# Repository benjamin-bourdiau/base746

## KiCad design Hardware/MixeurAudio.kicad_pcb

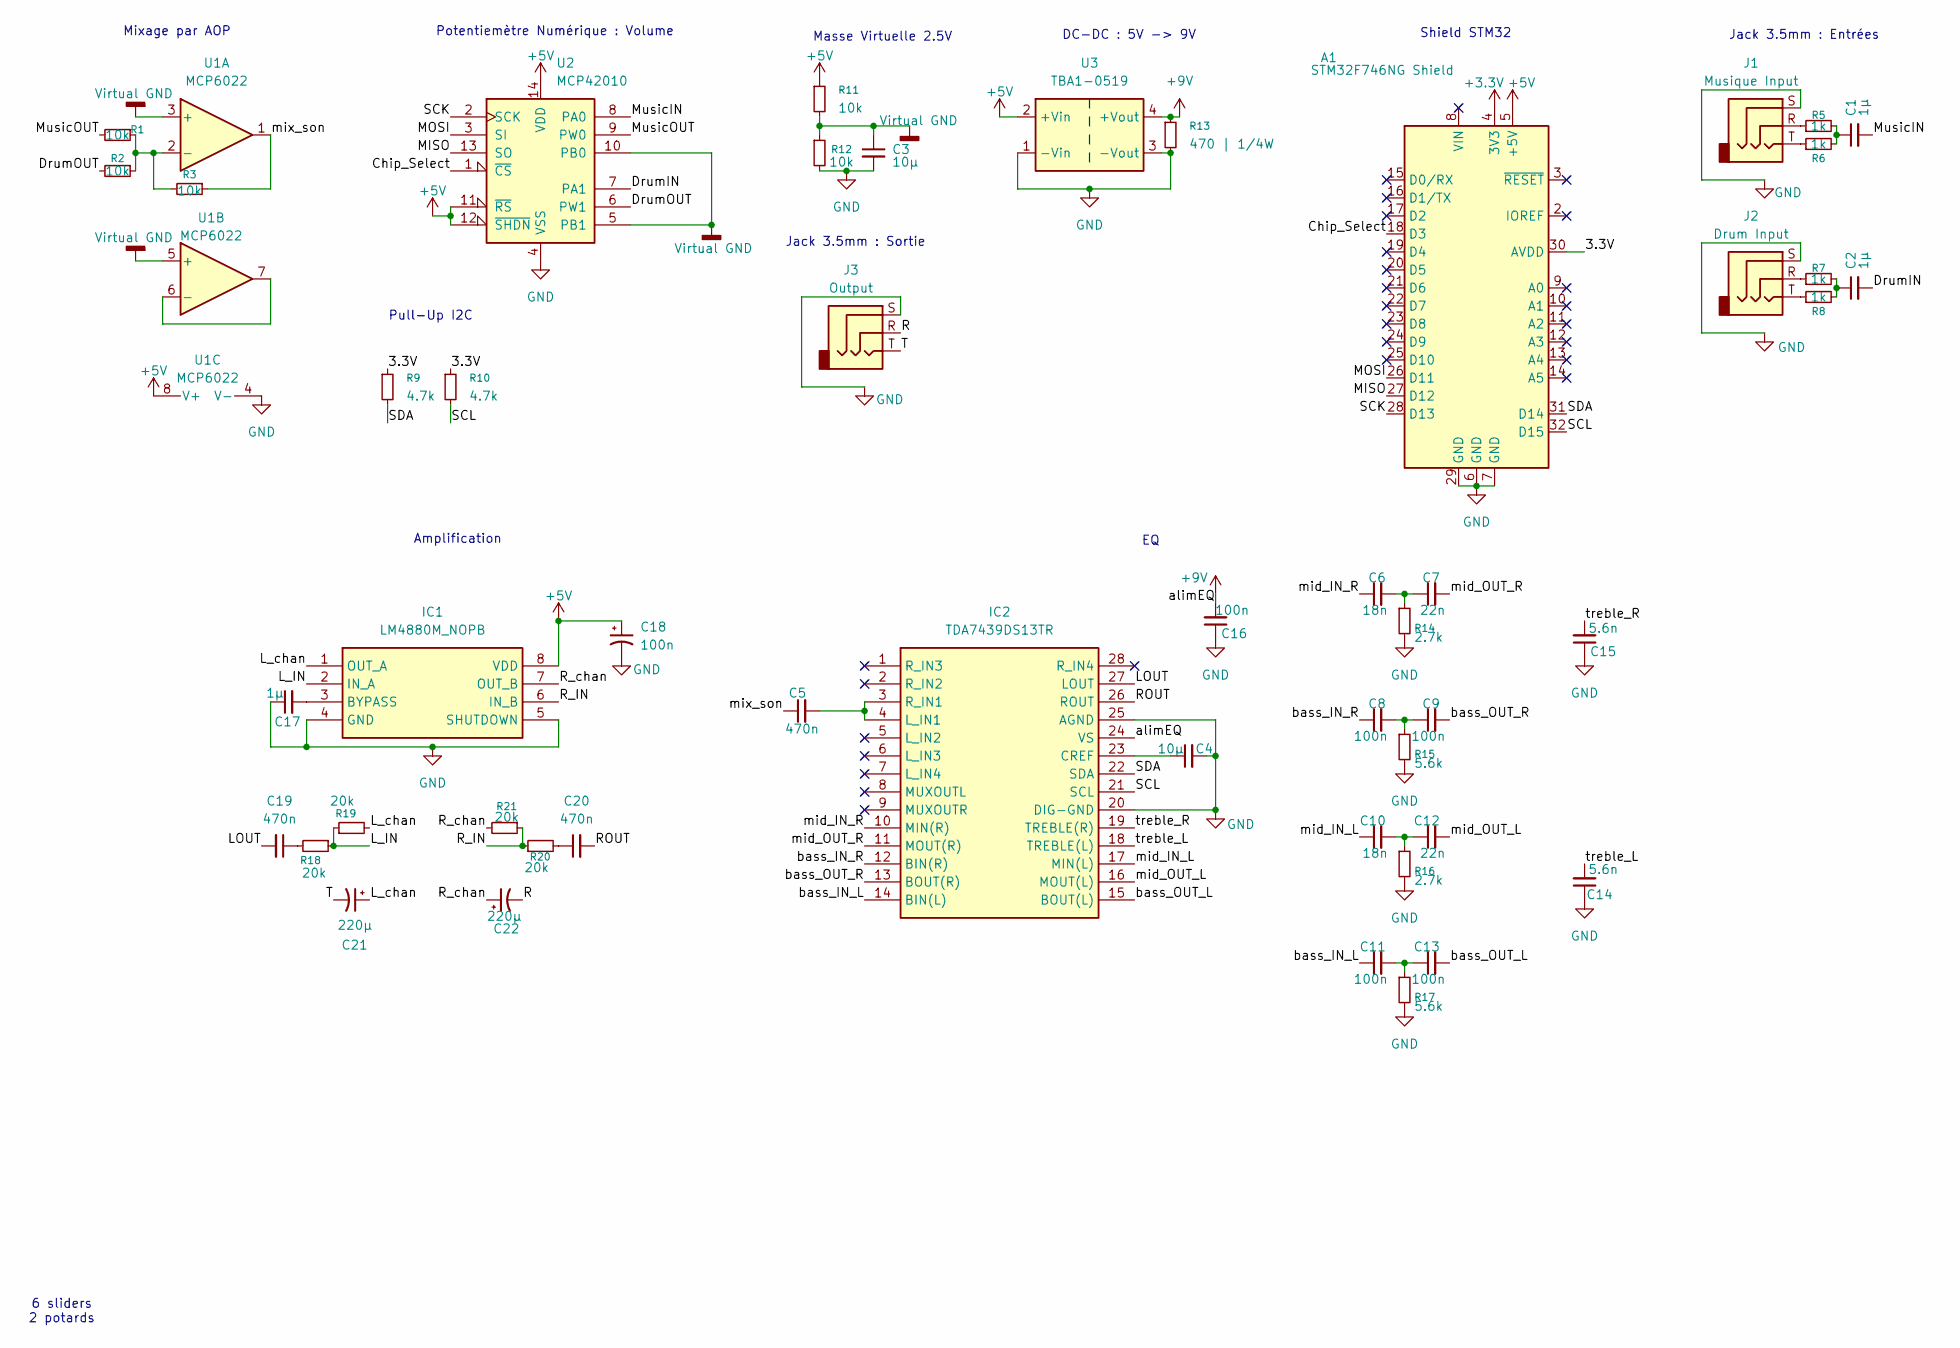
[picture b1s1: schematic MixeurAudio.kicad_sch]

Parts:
A1: STM32F746NG Shield; Arduino_UNO_R3
C1, C2, C17: 1µ; C_1206_3216Metric_Pad1.33x1.80mm_HandSolder
C3, C4: 10µ; C_1206_3216Metric_Pad1.33x1.80mm_HandSolder
C5, C19, C20: 470n; C_1206_3216Metric_Pad1.33x1.80mm_HandSolder
C6, C10: 18n; C_1206_3216Metric_Pad1.33x1.80mm_HandSolder
C7, C12: 22n; C_1206_3216Metric_Pad1.33x1.80mm_HandSolder
C8, C9, C11, C13, C16: 100n; C_1206_3216Metric_Pad1.33x1.80mm_HandSolder
C14, C15: 5.6n; C_1206_3216Metric_Pad1.33x1.80mm_HandSolder
C18: 100n; CP_Radial_D10.0mm_P3.80mm
C21, C22: 220µ; CP_Radial_D10.0mm_P3.80mm
IC1: LM4880M_NOPB; SOIC127P600X175-8N; Manufacturer_Part_Number LM4880M/NOPB; Mouser Part Number 595-LM4880M/NOPB
IC2: TDA7439DS13TR; SOIC127P1032X265-28N; Manufacturer_Part_Number TDA7439DS13TR; Mouser Part Number 511-TDA7439DS13TR
J1: Musique Input; JACK_KLBR_4_LMB
J2: Drum Input; JACK_KLBR_4_LMB
J3: Output; JACK_KLBR_4_LMB
R1, R2, R3, R11, R12: 10k; R_1206_3216Metric_Pad1.30x1.75mm_HandSolder
R5, R6, R7, R8: 1k; R_1206_3216Metric_Pad1.30x1.75mm_HandSolder
R9, R10: 4.7k; R_1206_3216Metric_Pad1.30x1.75mm_HandSolder
R13: 470 | 1/4W; R_1206_3216Metric_Pad1.30x1.75mm_HandSolder
R14, R16: 2.7k; R_1206_3216Metric_Pad1.30x1.75mm_HandSolder
R15, R17: 5.6k; R_1206_3216Metric_Pad1.30x1.75mm_HandSolder
R18, R19, R20, R21: 20k; R_1206_3216Metric_Pad1.30x1.75mm_HandSolder
U1: MCP6022; DIP-8_W7.62mm_Socket_LongPads
U2: MCP42010; DIP-14_W7.62mm_Socket_LongPads
U3: TBA1-0519; Converter_DCDC_TRACO_TBA1-xxxx_THT

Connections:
+3.3V: A1.4 (3V3)
+5V: A1.5 (+5V), C18.1, IC1.8 (VDD), R11.1, U1.8 (V+), U2.11 (~RS), U2.12 (~SHDN), U2.14 (VDD), U3.2 (+Vin)
+9V: C16.2, IC2.24 (VS), R13.1, U3.4 (+Vout)
/3.3V: A1.30 (AVDD), R9.1, R10.1
/Chip_Select: A1.18 (D3), U2.1 (~CS)
/DrumIN: C2.2, U2.7 (PA1)
/DrumOUT: R2.2, U2.6 (PW1)
/LOUT: C19.2, IC2.27 (LOUT)
/L_IN: IC1.2 (IN_A), R18.1, R19.1
/L_chan: C21.1, IC1.1 (OUT_A), R19.2
/MISO: A1.27 (D12), U2.13 (SO)
/MOSI: A1.26 (D11), U2.3 (SI)
/MusicIN: C1.2, U2.8 (PA0)
/MusicOUT: R1.2, U2.9 (PW0)
/R: C22.2, J3.R
/ROUT: C20.2, IC2.26 (ROUT)
/R_IN: IC1.6 (IN_B), R20.1, R21.1
/R_chan: C22.1, IC1.7 (OUT_B), R21.2
/SCK: A1.28 (D13), U2.2 (SCK)
/SCL: A1.32 (D15), IC2.21 (SCL), R10.2
/SDA: A1.31 (D14), IC2.22 (SDA), R9.2
/T: C21.2, J3.T
/bass_IN_L: C11.1, IC2.14 (BIN(L))
/bass_IN_R: C8.1, IC2.12 (BIN(R))
/bass_OUT_L: C13.2, IC2.15 (BOUT(L))
/bass_OUT_R: C9.2, IC2.13 (BOUT(R))
/mid_IN_L: C10.1, IC2.17 (MIN(L))
/mid_IN_R: C6.1, IC2.10 (MIN(R))
/mid_OUT_L: C12.2, IC2.16 (MOUT(L))
/mid_OUT_R: C7.2, IC2.11 (MOUT(R))
/mix_son: C5.1, R3.1, U1.1
/treble_L: C14.2, IC2.18 (TREBLE(L))
/treble_R: C15.2, IC2.19 (TREBLE(R))
GND: A1.6 (GND), A1.7 (GND), A1.29 (GND), C3.2, C4.2, C14.1, C15.1, C16.1, C17.1, C18.2, IC1.4 (GND), IC1.5 (SHUTDOWN), IC2.20 (DIG-GND), IC2.25 (AGND), J1.S, J2.S, J3.S, R12.2, R13.2, R14.2, R15.2, R16.2, R17.2, U1.4 (V-), U2.4 (VSS), U3.1 (-Vin), U3.3 (-Vout)
unnamed: C1.1, R5.2, R6.2
unnamed: C2.1, R7.2, R8.2
unnamed: C6.2, C7.1, R14.1
unnamed: C8.2, C9.1, R15.1
unnamed: C10.2, C12.1, R16.1
unnamed: C11.2, C13.1, R17.1
unnamed: C19.1, R18.2
unnamed: C20.1, R20.2
unnamed: C17.2, IC1.3 (BYPASS)
unnamed: C4.1, IC2.23 (CREF)
unnamed: C5.2, IC2.3 (R_IN1), IC2.4 (L_IN1)
unnamed: J1.R, R5.1
unnamed: J1.T, R6.1
unnamed: J2.R, R7.1
unnamed: J2.T, R8.1
unnamed: R1.1, R2.1, R3.2, U1.2 (-)
unnamed: U1.6 (-), U1.7
Virtual GND: C3.1, R11.2, R12.1, U1.3 (+), U1.5 (+), U2.5 (PB1), U2.10 (PB0)

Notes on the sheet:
Mixage par AOP
Masse Virtuelle 2.5V
Shield STM32
DC-DC : 5V -> 9V
Jack 3.5mm : Sortie
Potentiemètre Numérique : Volume
6 sliders 2 potards
Jack 3.5mm : Entrées
Amplification
Pull-Up I2C

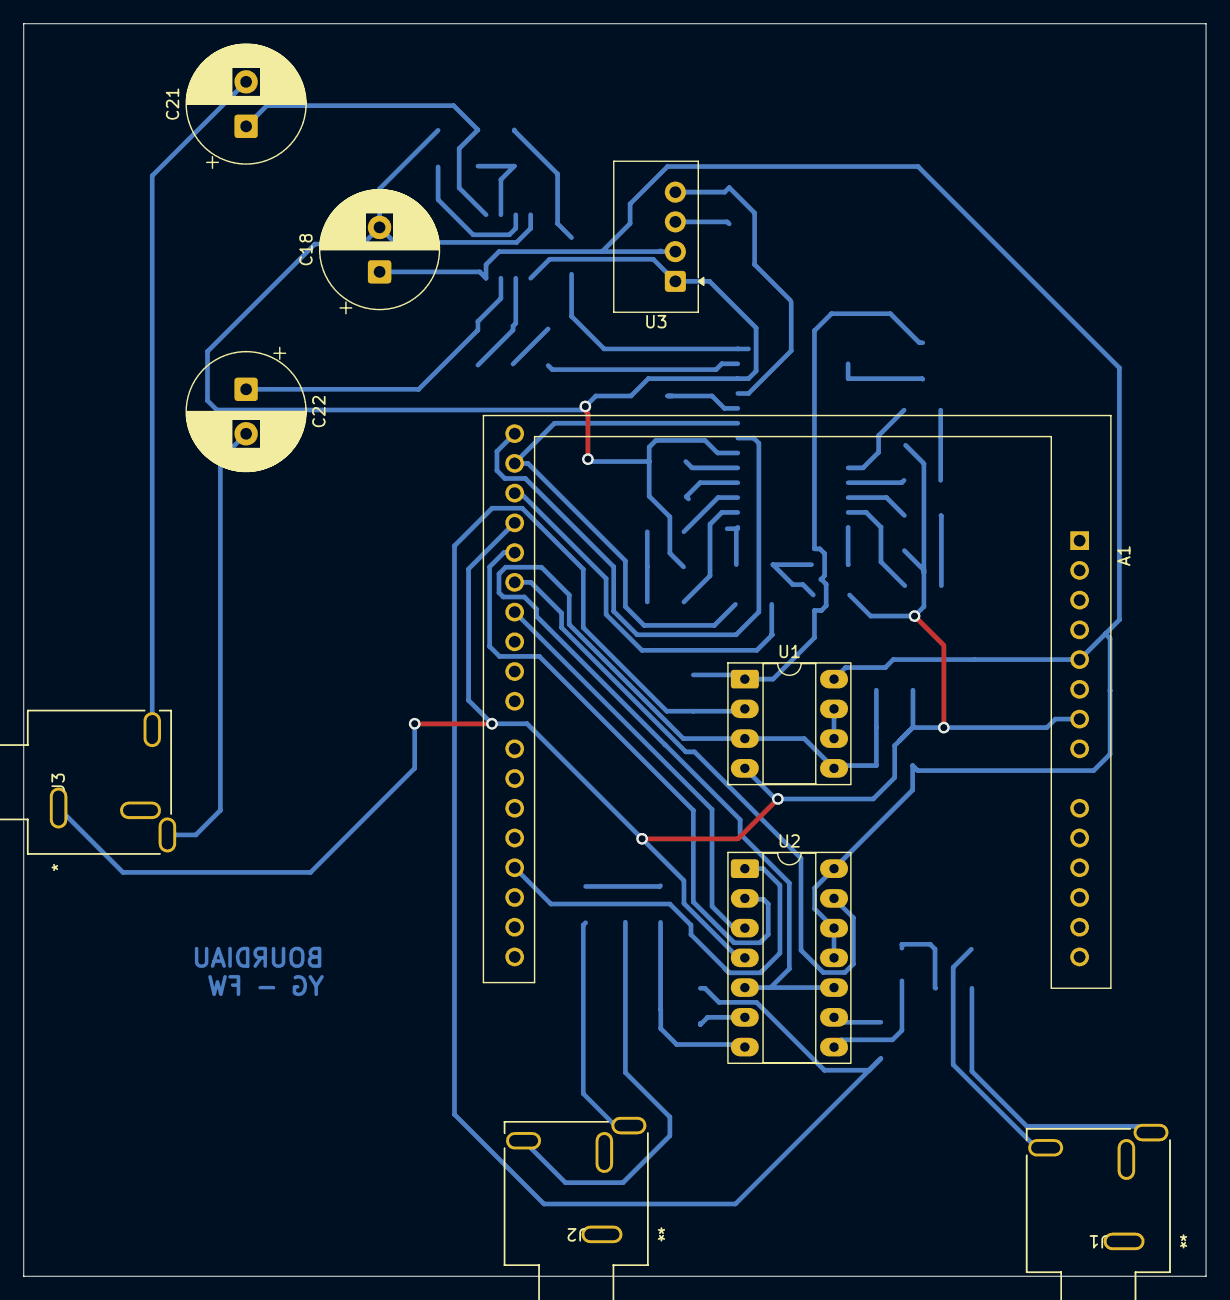
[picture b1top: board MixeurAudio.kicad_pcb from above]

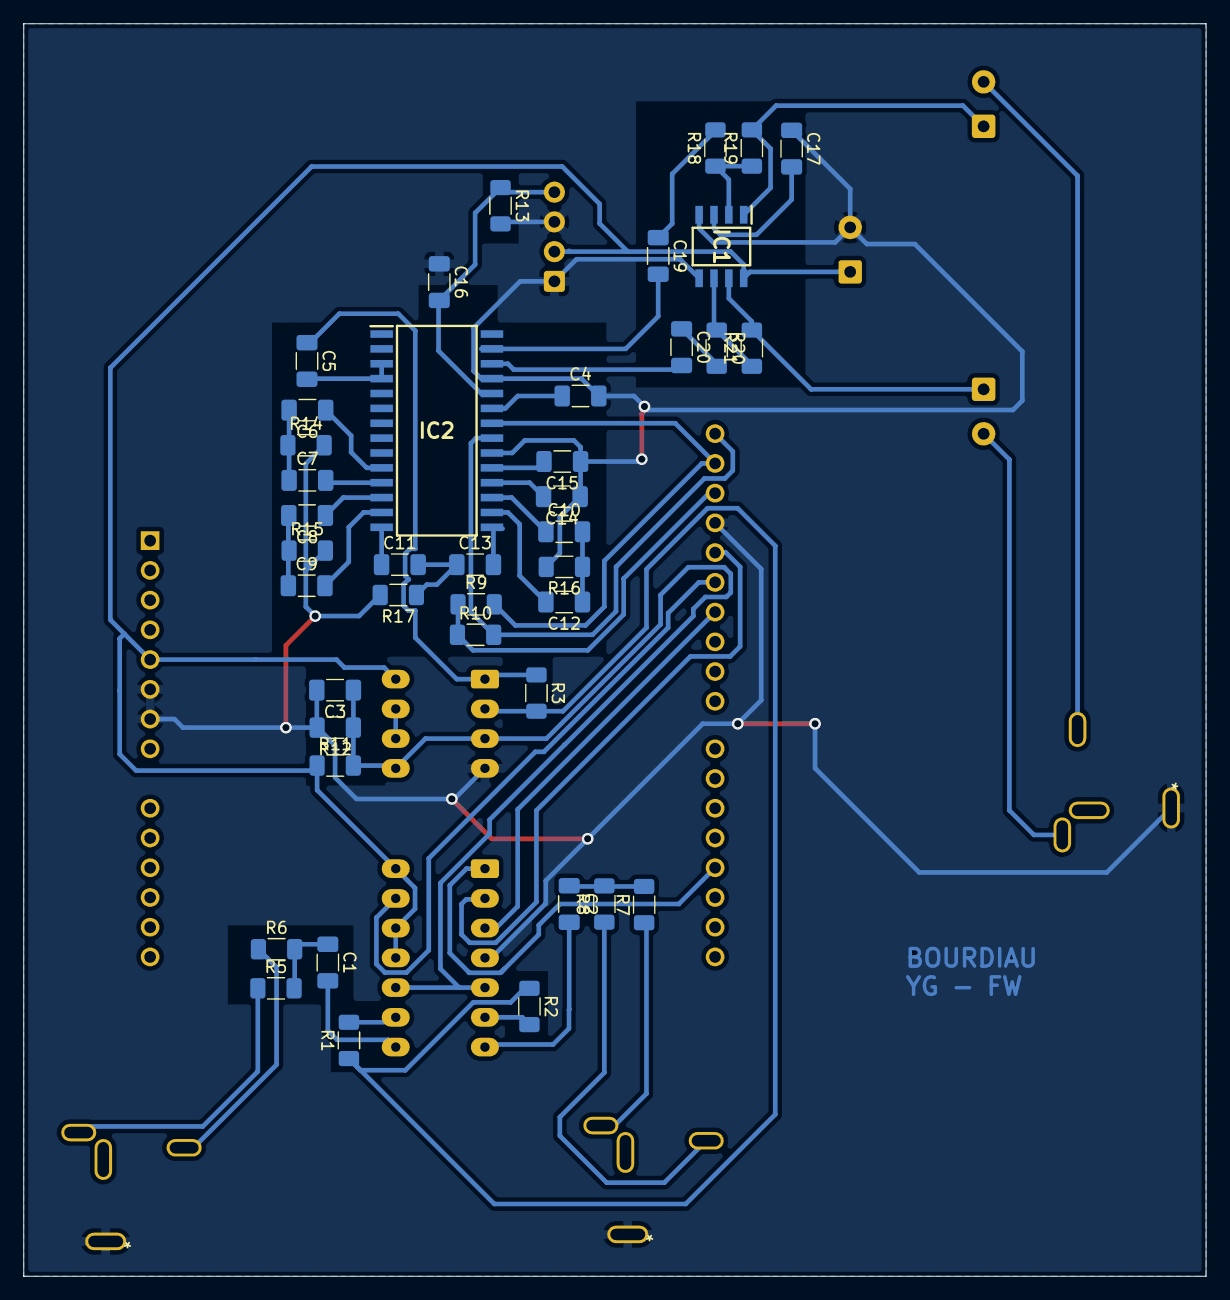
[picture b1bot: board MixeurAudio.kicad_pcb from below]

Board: 2 copper layers, 101.0 x 107.0 mm, 51 parts (41 on the bottom side), 51 nets.

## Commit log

2026-05-27 changement fond + slider 1
2026-05-28 6 sliders + 2 potards in case
2026-06-03 TDA et MCP fonctionnel
2026-06-04 le vrai code qui marche vraiment l'autre c fake
2026-06-04 gestion treble
2026-06-04 gestion lock unlock EQ
2026-06-04 truc qui marche v1
2026-06-09 volume + EQ + ~IHM
2026-06-09 valeurs start EQ + Volume set en dur
2026-06-09 knob = image.png
2026-06-09 knob img fonctionnel + debut potards
2026-06-11 potard fonctionnel + slider fonctionnel : on est sur du fignolage
2026-06-11 led de mute
2026-06-15 code final commenté
2026-06-19 Reconstruction : Ajout KiCad
